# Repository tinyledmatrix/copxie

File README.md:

# copxie
Small project inspired by #PIXIE. Software and Firmware compatible but using discrete LEDs instead of dot Matrix modules

see https://hackaday.io/project/174310-copxie-chainable-dual-57-tiny-led-matrix for more information

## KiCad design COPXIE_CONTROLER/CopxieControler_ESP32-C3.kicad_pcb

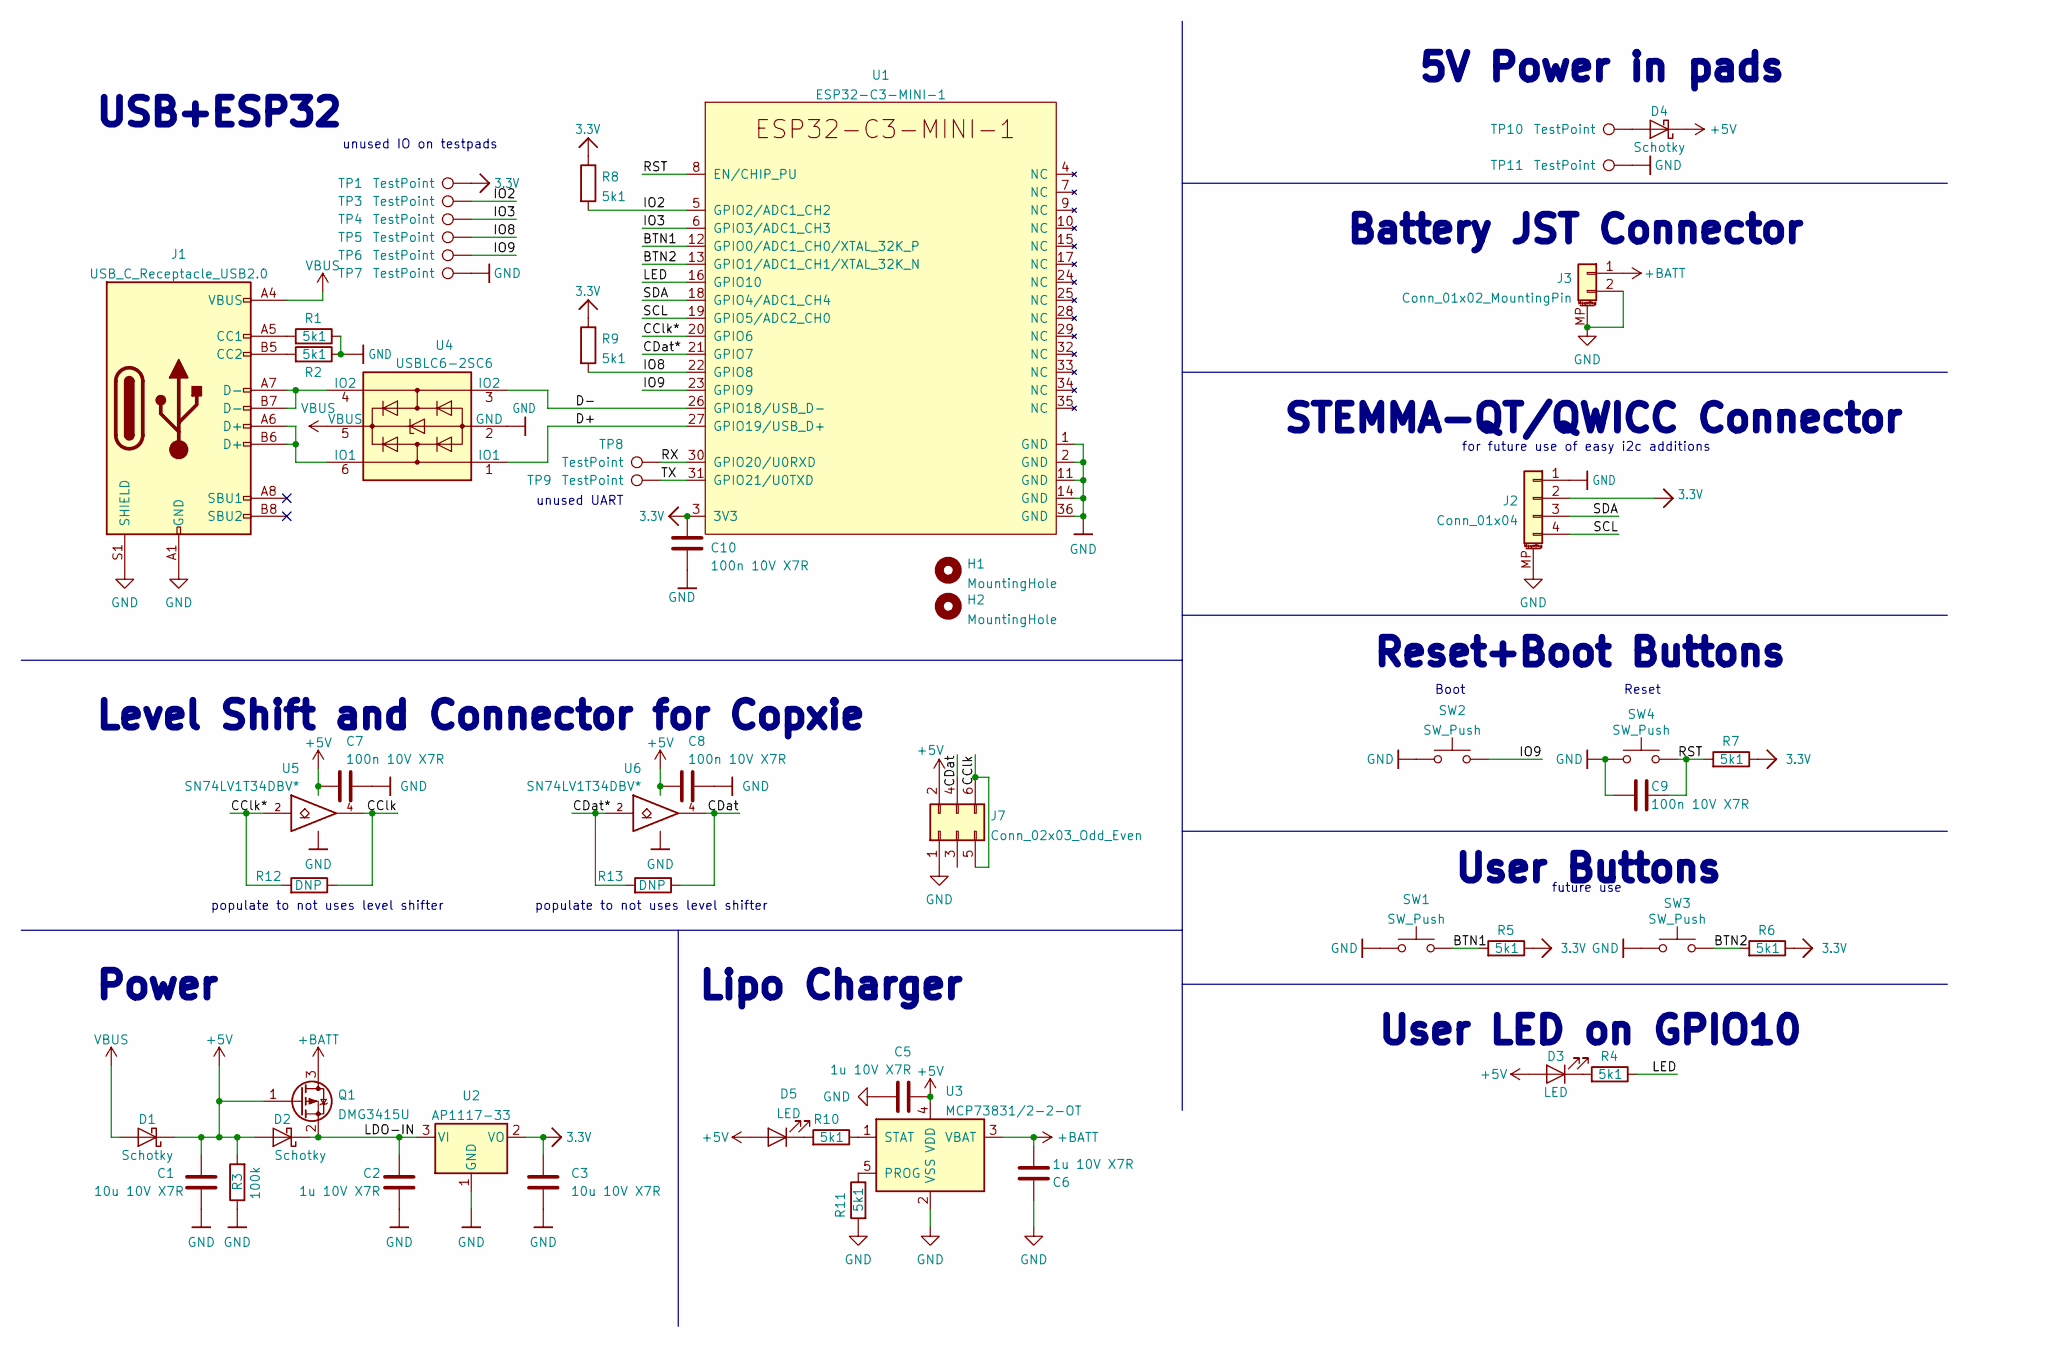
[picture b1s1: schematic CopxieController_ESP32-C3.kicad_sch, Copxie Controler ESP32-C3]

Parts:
C1: 10u 10V X7R; C_0603; Part# GRM155C80J106ME11D; LCSC# C237279
C2, C5, C6: 1u 10V X7R; C_0603; Mouser# 81-GRM033C81A105ME5D
C3: 10u 10V X7R; C_0603; Mouser# 81-GRM033C81A105ME5D
C7, C8, C9, C10: 100n 10V X7R; C_0603
D1, D2, D4: Schotky; D_SOD-123F
D3, D5: LED; LED_0603_1608Metric
H1, H2: MountingHole; MountingHole_2.5mm
J1: USB_C_Receptacle_USB2.0; USB_C_Receptacle_GT-USB-7010
J2: Conn_01x04; JST_SH_SM04B-SRSS-TB_1x04-1MP_P1.00mm_Horizontal; Part# SM04B-SRSS-TB(LF)(SN); LCSC# C160404
J3: Conn_01x02_MountingPin; JST_PH_S2B-PH-SM4-TB_1x02-1MP_P2.00mm_Horizontal
J7: Conn_02x03_Odd_Even; PinSocket_2x03_P2.54mm_Vertical
Q1: DMG3415U; SOT-23
R1, R2, R4, R5, R6, R7, R8, R9, R10, R11: 5k1; R_0603
R3: 100k; R_0603
R12, R13: DNP; R_0603
SW1, SW2, SW3, SW4: SW_Push; SW_Push_1P1T_NO_6x6mm_H9.5mm
TP1, TP3, TP4, TP5, TP6, TP7, TP8, TP9, TP10, TP11: TestPoint; PAD_SMD_R_1x1
U1: ESP32-C3-MINI-1
U2: AP1117-33; SOT-223-3_TabPin2
U3: MCP73831/2-2-OT; SOT-23-5
U4: USBLC6-2SC6; SOT-23-6
U5, U6: SN74LV1T34DBV*; SOT-23-5; LCSC# C100024

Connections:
3.3V: C3.1, C10.2, J2.2, R5.1, R6.1, R7.1, R8.1, R9.1, TP1.1, U1.3 (3V3), U2.2 (VO)
+5V: C1.1, C5.1, C7.1, C8.1, D1.1 (K), D2.2 (A), D3.2 (A), D4.1 (K), D5.2 (A), J7.2, Q1.1 (G), R3.2, U3.4 (VDD), U5.5 (VCC), U6.5 (VCC)
+BATT: C6.2, J3.1, Q1.3 (D), U3.3 (VBAT)
/BTN1: R5.2, SW1.2, U1.12 (GPIO0/ADC1_CH0/XTAL_32K_P)
/BTN2: R6.2, SW3.2, U1.13 (GPIO1/ADC1_CH1/XTAL_32K_N)
/CClk: J7.5, J7.6, R12.1, U5.4
/CClk*: R12.2, U1.20 (GPIO6), U5.2
/CDat: J7.4, R13.1, U6.4
/CDat*: R13.2, U1.21 (GPIO7), U6.2
/D+: U1.27 (GPIO19/USB_D+), U4.1 (IO1)
/D-: U1.26 (GPIO18/USB_D-), U4.3 (IO2)
/IO2: R8.2, TP3.1, U1.5 (GPIO2/ADC1_CH2)
/IO3: TP4.1, U1.6 (GPIO3/ADC1_CH3)
/IO8: R9.2, TP5.1, U1.22 (GPIO8)
/IO9: SW2.2, TP6.1, U1.23 (GPIO9)
/LDO-IN: C2.1, D2.1 (K), Q1.2 (S), U2.3 (VI)
/LED: R4.1, U1.16 (GPIO10)
/RST: C9.2, R7.2, SW4.2, U1.8 (EN/CHIP_PU)
/RX: TP8.1, U1.30 (GPIO20/U0RXD)
/SCL: J2.4, U1.19 (GPIO5/ADC2_CH0)
/SDA: J2.3, U1.18 (GPIO4/ADC1_CH4)
/TX: TP9.1, U1.31 (GPIO21/U0TXD)
GND: C1.2, C2.2, C3.2, C5.2, C6.1, C7.2, C8.2, C9.1, C10.1, J1.A1 (GND), J1.A12 (GND), J1.B1 (GND), J1.B12 (GND), J1.S1 (SHIELD), J2.1, J2.MP (MountPin), J3.2, J3.MP (MountPin), J7.1, R1.1, R2.1, R3.1, R11.2, SW1.1, SW2.1, SW3.1, SW4.1, TP7.1, TP11.1, U1.1 (GND), U1.2 (GND), U1.11 (GND), U1.14 (GND), U1.36 (GND), U2.1 (GND), U3.2 (VSS), U4.2 (GND), U5.3 (GND), U6.3 (GND)
unnamed: D3.1 (K), R4.2
unnamed: D4.2 (A), TP10.1
unnamed: D5.1 (K), R10.2
unnamed: J1.A5 (CC1), R1.2
unnamed: J1.A6 (D+), J1.B6 (D+), U4.6 (IO1)
unnamed: J1.A7 (D-), J1.B7 (D-), U4.4 (IO2)
unnamed: J1.B5 (CC2), R2.2
unnamed: R10.1, U3.1 (STAT)
unnamed: R11.1, U3.5 (PROG)
VBUS: D1.2 (A), J1.A4 (VBUS), J1.A9 (VBUS), J1.B4 (VBUS), J1.B9 (VBUS), U4.5 (VBUS)

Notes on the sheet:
Boot
Power
populate to not uses level shifter
Lipo Charger
Reset
STEMMA-QT/QWICC Connector
Level Shift and Connector for Copxie
5V Power in pads
User LED on GPIO10
User Buttons
future use
USB+ESP32
Battery JST Connector
unused IO on testpads
Reset+Boot Buttons
unused UART
for future use of easy i2c additions

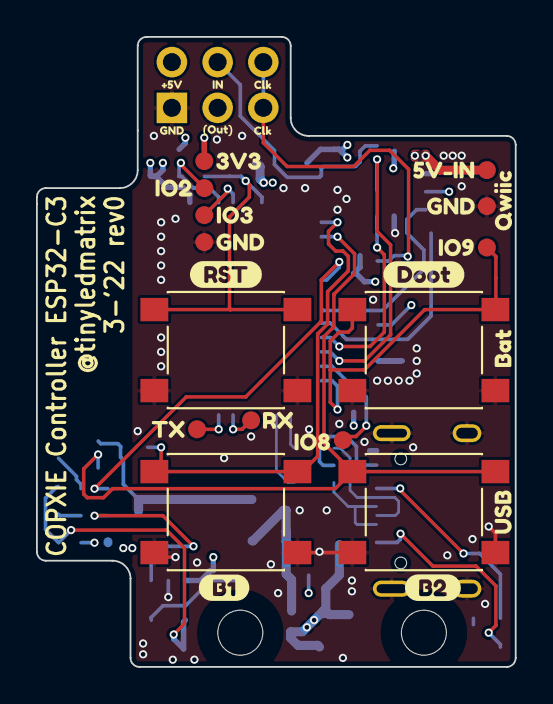
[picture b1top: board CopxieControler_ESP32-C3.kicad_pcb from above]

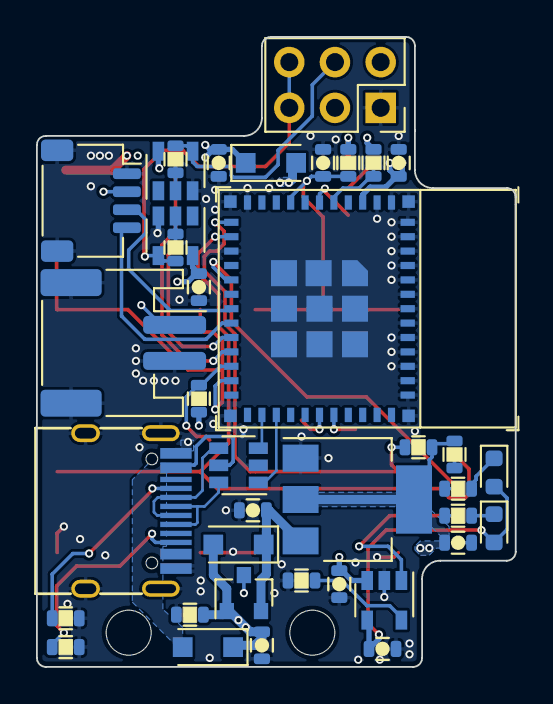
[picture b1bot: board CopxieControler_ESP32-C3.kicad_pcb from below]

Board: 4 copper layers, 26.6 x 35.0 mm, 77 parts (38 on the bottom side), 33 nets.

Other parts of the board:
kibuzzard-623257AE: G***; kibuzzard-623257AE
kibuzzard-623257C1: G***; kibuzzard-623257C1
kibuzzard-623257D1: G***; kibuzzard-623257D1
kibuzzard-623257DD: G***; kibuzzard-623257DD
kibuzzard-623258FD: G***; kibuzzard-623258FD
kibuzzard-623262B1: G***; kibuzzard-623262B1
kibuzzard-623262C8: G***; kibuzzard-623262C8
kibuzzard-623262EA: G***; kibuzzard-623262EA
kibuzzard-623262F8: G***; kibuzzard-623262F8
kibuzzard-6232576D: G***; kibuzzard-6232576D
kibuzzard-6232578A: G***; kibuzzard-6232578A
kibuzzard-6232587E: G***; kibuzzard-6232587E
kibuzzard-6232592F: G***; kibuzzard-6232592F
kibuzzard-62325757: G***; kibuzzard-62325757
kibuzzard-62325762: G***; kibuzzard-62325762
kibuzzard-62325779: G***; kibuzzard-62325779
kibuzzard-62325798: G***; kibuzzard-62325798
kibuzzard-62325817: G***; kibuzzard-62325817
kibuzzard-62325827: G***; kibuzzard-62325827
kibuzzard-62325857: G***; kibuzzard-62325857
kibuzzard-62325914: G***; kibuzzard-62325914
kibuzzard-62326280, kibuzzard-62326280#2: G***; kibuzzard-62326280

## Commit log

2022-10-17 Kicad push
2022-10-18 typo fix
